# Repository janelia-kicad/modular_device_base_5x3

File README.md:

- [Repository Information](#org3363df3)
  - [Description](#orgd222b12)
- [Images](#orga7265e7)
- [Schematic](#orgfcf2128)
- [Gerbers](#org41eb2be)
- [Bill of Materials](#org5237e5d)
  - [PCB Parts](#org7a5a6dd)
  - [Supplemental Parts](#org5971931)
  - [Vendor Parts Lists](#orgb088364)
- [Supplemental Documentation](#org552370b)
  - [Assembly Instructions](#org9c28d25)

# Repository Information

-   **Name:** modular\_device\_base\_5x3
-   **Version:** 1.2
-   **License:** Open-Source Hardware
-   **URL:** <https://github.com/janelia-kicad/modular_device_base_5x3>
-   **Author:** Peter Polidoro
-   **Email:** peterpolidoro@gmail.com

## Description

This board is the base of 5x3 format modular devices. It is a breakout board for the microprocessor, with connections for power, communication, and top boards.

# Images

# Schematic

[./schematic/modular\_device\_base\_5x3.pdf](./schematic/modular_device_base_5x3.pdf)

# Gerbers

Send gerbers zip file to your favorite PCB manufacturer for fabrication.

[./gerbers/modular\_device\_base\_5x3\_v1.2.zip](./gerbers/modular_device_base_5x3_v1.2.zip)

# Bill of Materials

## PCB Parts

| Item | Reference(s)                         | Quantity | PartNumber          | Vendor  | Description                                           |
|---- |------------------------------------ |-------- |------------------- |------- |----------------------------------------------------- |
| 1    | C1 C2 C3 C4 C5                       | 5        | 445-4536-1-ND       | digikey | CAP CER 10UF 50V 10% X7S 1210                         |
| 2    | C6                                   | 1        | 399-13229-1-ND      | digikey | CAP CER 0.1UF 100V X7R 1210                           |
| 3    | D1 D2                                | 2        | LSM115JE3/TR13CT-ND | digikey | DIODE SCHOTTKY 15V 1A DO214BA                         |
| 4    | D10 D11 D12 D13 D3 D4 D5 D6 D7 D8 D9 | 11       | 568-11697-1-ND      | digikey | DIODE SCHOTTKY 45V 10A CFP15                          |
| 5    | L1                                   | 1        | 350-1712-ND         | digikey | LED 2MM 5V RT ANGLE RED PCMNT                         |
| 6    | L2                                   | 1        | 350-1717-ND         | digikey | LED 2MM 5V RT ANGLE GREEN PCMNT                       |
| 7    | L3                                   | 1        | 350-1719-ND         | digikey | LED 2MM 5V RT ANGLE YELLOW PCMNT                      |
| 8    | MDB1                                 | 2        | S7058-ND            | digikey | 25 Position Header Through Hole Female Socket         |
| 9    | MH1 MH2 MH3 MH4 MH5 MH6 MH7 MH8      | 8        | 36-2027-ND          | digikey | Round Standoff Threaded 4-40 Aluminum 0.500in 0.187in |
| 10   | P1                                   | 1        | CP-063BH-ND         | digikey | CONN PWR JACK DC 2.5X5.5 8A T/H                       |
| 11   | P10 P4 P6 P8                         | 4        | A100903CT-ND        | digikey | CONN HEADER 2POS R/A SMD GOLD                         |
| 12   | P11                                  | 1        | 732-5336-ND         | digikey | CONN HEADER 3 POS RA 2.54                             |
| 13   | P12 P13                              | 2        | SAM10781-ND         | digikey | CONN HEADER 2POS .100in SNGL SMD                      |
| 14   | P2                                   | 1        | ACX1655-ND          | digikey | CONN BNC JACK R/A 75 OHM PCB                          |
| 15   | P3 P5 P7 P9                          | 4        | A100890CT-ND        | digikey | CONN HEADER 3POS R/A SMD GOLD                         |
| 16   | R1                                   | 1        | P6.19KAACT-ND       | digikey | RES SMD 6.19K OHM 1% 1/2W 1210                        |
| 17   | REG1                                 | 1        | 945-1395-5-ND       | digikey | CONV DC/DC 1A 5V OUT SIP VERT                         |
| 18   | SW1 SW2                              | 2        | CKN1860CT-ND        | digikey | SWITCH TACTILE SPST-NO 1VA 32V                        |
| 19   | TEENSY1                              | 1        | 1568-1443-ND        | digikey | TEENSY 3.5                                            |
| 20   | U1                                   | 1        | MAX6817EUT+TCT-ND   | digikey | IC DEBOUNCER SWITCH DUAL SOT23-6                      |

## Supplemental Parts

| Item | Quantity | PartNumber    | Vendor  | Description                                                              |
|---- |-------- |------------- |------- |------------------------------------------------------------------------ |
| 1    | 1        | 62-1187-ND    | digikey | AC/DC DESKTOP ADAPTER 24V 90W                                            |
| 2    | 1        | 993-1037-ND   | digikey | CORD 3COND NEMA PLUG 320-C5                                              |
| 3    | 2        | A106625CT-ND  | digikey | 14 Positions Header Unshrouded Breakaway Connector 0.100in 2 row SMD     |
| 4    | 3        | S1011EC-24-ND | digikey | 14 Positions Header Unshrouded Breakaway Connector 0.100in 1 row Through |
| 5    | 1        | S9001-ND      | digikey | CONN JUMPER SHORTING GOLD FLASH                                          |
| 6    | 1        | AE10342-ND    | digikey | CABLE USB-A TO MICRO USB-B 2M                                            |
| 7    | 2        | 492-1077-ND   | digikey | ROUND SPACER 4 NYLON 7/16in                                              |

## Vendor Parts Lists

[./bom/digikey\_parts.csv](./bom/digikey_parts.csv)

[./bom/supplemental\_digikey\_parts.csv](./bom/supplemental_digikey_parts.csv)

# Supplemental Documentation

## Assembly Instructions

-   Cut the bottom trace on the Teensy board that connects the 5V pads according to these instructions <https://www.pjrc.com/teensy/external_power.html>.
-   Solder through hole header pins into every Teensy 0.1 inch header hole.
-   Solder surface mount header pins onto the bottom of the Teensy making sure they are properly aligned.
-   Solder surface mount and through hole components onto the pcb.
-   Solder the Teensy into the pcb making sure it is properly aligned.
-   Connect header jumper to RED LED enable pins.

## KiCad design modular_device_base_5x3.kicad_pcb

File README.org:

# Created 2018-05-18 Fri 09:39
#+OPTIONS: title:nil author:nil email:nil toc:t |:t ^:nil
* Repository Information

- Name :: modular_device_base_5x3
- Version :: 1.2
- License :: Open-Source Hardware
- URL :: https://github.com/janelia-kicad/modular_device_base_5x3
- Author :: Peter Polidoro
- Email :: peterpolidoro@gmail.com

** Description

This board is the base of 5x3 format modular devices. It is a breakout board
for the microprocessor, with connections for power, communication, and top
boards.

* Images

[[file:./images/top.png]]

[[file:./images/bottom.png]]

* Schematic

[[file:./schematic/modular_device_base_5x3.pdf][./schematic/modular_device_base_5x3.pdf]]

[[file:./schematic/images/schematic00.png]]

* Gerbers

Send gerbers zip file to your favorite PCB manufacturer for fabrication.

[[file:./gerbers/modular_device_base_5x3_v1.2.zip][./gerbers/modular_device_base_5x3_v1.2.zip]]

[[file:./gerbers/images/gerbers00.png]]

[[file:./gerbers/images/gerbers01.png]]

* Bill of Materials

** PCB Parts

| Item | Reference(s)                         | Quantity | PartNumber          | Vendor  | Description                                           |
|------+--------------------------------------+----------+---------------------+---------+-------------------------------------------------------|
|    1 | C1 C2 C3 C4 C5                       |        5 | 445-4536-1-ND       | digikey | CAP CER 10UF 50V 10% X7S 1210                         |
|    2 | C6                                   |        1 | 399-13229-1-ND      | digikey | CAP CER 0.1UF 100V X7R 1210                           |
|    3 | D1 D2                                |        2 | LSM115JE3/TR13CT-ND | digikey | DIODE SCHOTTKY 15V 1A DO214BA                         |
|    4 | D10 D11 D12 D13 D3 D4 D5 D6 D7 D8 D9 |       11 | 568-11697-1-ND      | digikey | DIODE SCHOTTKY 45V 10A CFP15                          |
|    5 | L1                                   |        1 | 350-1712-ND         | digikey | LED 2MM 5V RT ANGLE RED PCMNT                         |
|    6 | L2                                   |        1 | 350-1717-ND         | digikey | LED 2MM 5V RT ANGLE GREEN PCMNT                       |
|    7 | L3                                   |        1 | 350-1719-ND         | digikey | LED 2MM 5V RT ANGLE YELLOW PCMNT                      |
|    8 | MDB1                                 |        2 | S7058-ND            | digikey | 25 Position Header Through Hole Female Socket         |
|    9 | MH1 MH2 MH3 MH4 MH5 MH6 MH7 MH8      |        8 | 36-2027-ND          | digikey | Round Standoff Threaded 4-40 Aluminum 0.500in 0.187in |
|   10 | P1                                   |        1 | CP-063BH-ND         | digikey | CONN PWR JACK DC 2.5X5.5 8A T/H                       |
|   11 | P10 P4 P6 P8                         |        4 | A100903CT-ND        | digikey | CONN HEADER 2POS R/A SMD GOLD                         |
|   12 | P11                                  |        1 | 732-5336-ND         | digikey | CONN HEADER 3 POS RA 2.54                             |
|   13 | P12 P13                              |        2 | SAM10781-ND         | digikey | CONN HEADER 2POS .100in SNGL SMD                      |
|   14 | P2                                   |        1 | ACX1655-ND          | digikey | CONN BNC JACK R/A 75 OHM PCB                          |
|   15 | P3 P5 P7 P9                          |        4 | A100890CT-ND        | digikey | CONN HEADER 3POS R/A SMD GOLD                         |
|   16 | R1                                   |        1 | P6.19KAACT-ND       | digikey | RES SMD 6.19K OHM 1% 1/2W 1210                        |
|   17 | REG1                                 |        1 | 945-1395-5-ND       | digikey | CONV DC/DC 1A 5V OUT SIP VERT                         |
|   18 | SW1 SW2                              |        2 | CKN1860CT-ND        | digikey | SWITCH TACTILE SPST-NO 1VA 32V                        |
|   19 | TEENSY1                              |        1 | 1568-1443-ND        | digikey | TEENSY 3.5                                            |
|   20 | U1                                   |        1 | MAX6817EUT+TCT-ND   | digikey | IC DEBOUNCER SWITCH DUAL SOT23-6                      |

** Supplemental Parts

| Item | Quantity | PartNumber    | Vendor  | Description                                                              |
|------+----------+---------------+---------+--------------------------------------------------------------------------|
|    1 |        1 | 62-1187-ND    | digikey | AC/DC DESKTOP ADAPTER 24V 90W                                            |
|    2 |        1 | 993-1037-ND   | digikey | CORD 3COND NEMA PLUG 320-C5                                              |
|    3 |        2 | A106625CT-ND  | digikey | 14 Positions Header Unshrouded Breakaway Connector 0.100in 2 row SMD     |
|    4 |        3 | S1011EC-24-ND | digikey | 14 Positions Header Unshrouded Breakaway Connector 0.100in 1 row Through |
|    5 |        1 | S9001-ND      | digikey | CONN JUMPER SHORTING GOLD FLASH                                          |
|    6 |        1 | AE10342-ND    | digikey | CABLE USB-A TO MICRO USB-B 2M                                            |
|    7 |        2 | 492-1077-ND   | digikey | ROUND SPACER 4 NYLON 7/16in                                              |

** Vendor Parts Lists

[[file:./bom/digikey_parts.csv][./bom/digikey_parts.csv]]

[[file:./bom/supplemental_digikey_parts.csv][./bom/supplemental_digikey_parts.csv]]

* Supplemental Documentation

** Assembly Instructions

- Cut the bottom trace on the Teensy board that connects the 5V pads according
  to these instructions [[https://www.pjrc.com/teensy/external_power.html]].
- Solder through hole header pins into every Teensy 0.1 inch header hole.
- Solder surface mount header pins onto the bottom of the Teensy making sure
  they are properly aligned.
- Solder surface mount and through hole components onto the pcb.
- Solder the Teensy into the pcb making sure it is properly aligned.
- Connect header jumper to RED LED enable pins.

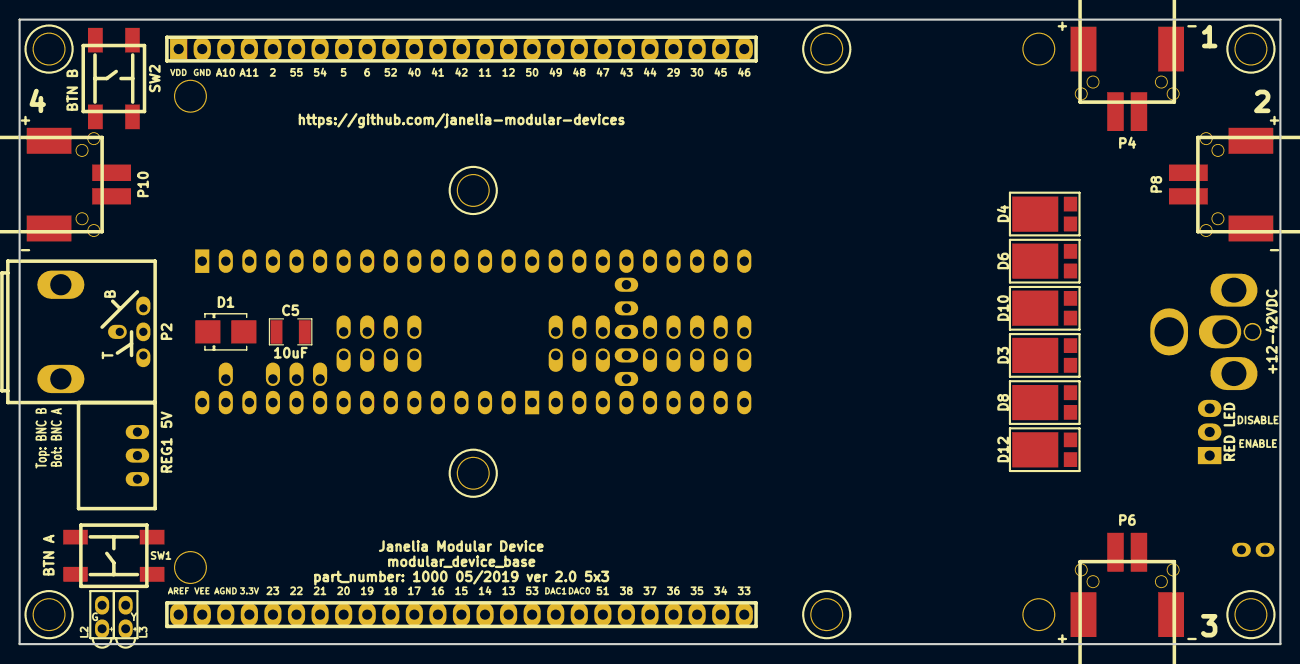
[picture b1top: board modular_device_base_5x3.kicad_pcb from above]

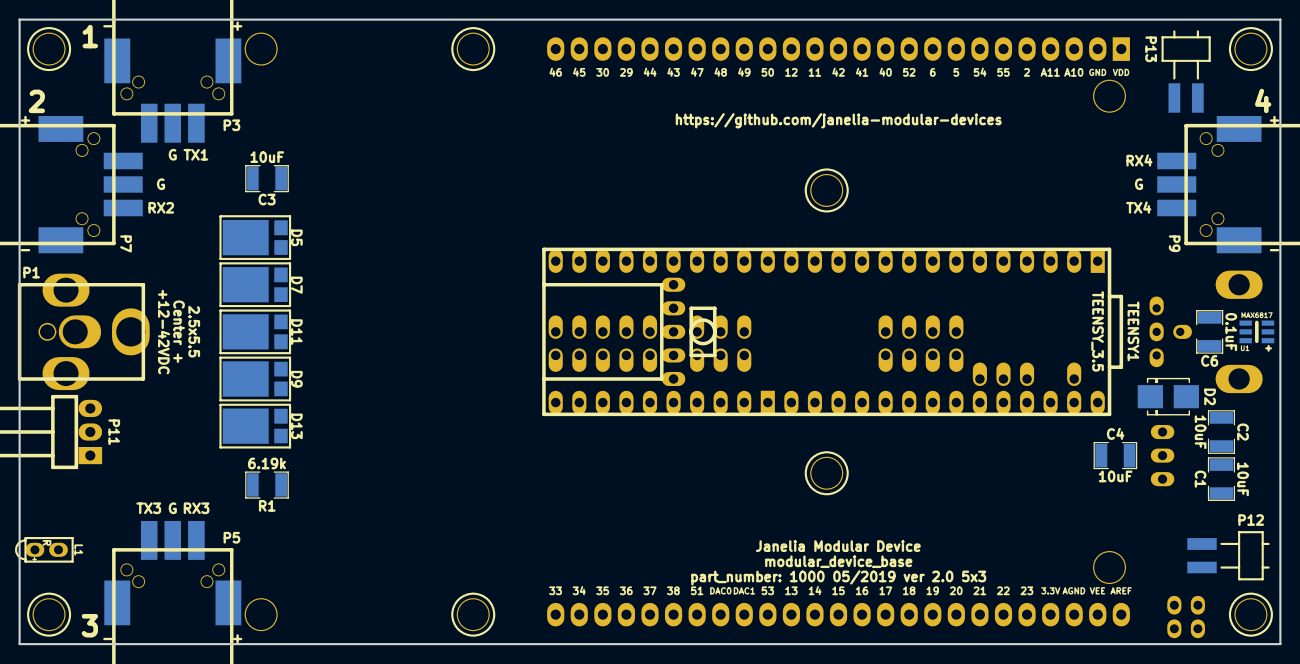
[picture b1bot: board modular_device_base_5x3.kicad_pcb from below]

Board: 2 copper layers, 135.9 x 67.3 mm, 50 parts (23 on the bottom side), 76 nets, no tracks yet.

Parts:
C1, C2, C3, C4, C5: 10uF; SM1210
C6: 0.1uF; SM1210
D1, D2: diode_schottky_15V_1A; DO-214BA
D3, D4, D5, D6, D7, D8, D9, D10, D11, D12, D13: diode_schottky_45V_10A; CFP15
L1: LED_5V_RED_RA; LED_555-2XXX
L2: LED_5V_GRN_RA; LED_555-2XXX
L3: LED_5V_YEL_RA; LED_555-2XXX
MDB1: MODULAR_DEVICE_BASE_5x3_FEMALE; MODULAR_DEVICE_BASE_5X3_FEMALE
MH1, MH2, MH3, MH4, MH5, MH6, MH7, MH8: MNT_HOLE; MOUNTING_HOLE_4-40
P1: PWR_JACK_2.5x5.5; DCJACK_2PIN_HIGHCURRENT
P2: BNC_DOUBLE_RA; BNC_DOUBLE
P3, P5, P7, P9: HEADER_01X03_SMD_RA; Header_3_Pin_SMD_RA
P4, P6, P8, P10: HEADER_01X02_SMD_RA; Header_2_Pin_SMD_RA
P11: HEADER_01X03_RA; Header_3_Pin_RA
P12, P13: HEADER_01X02_SMD_RA_UNSHR; Header_2_Pin_SMD_RA_UNSHR
R1: 6.19k; SM1210
REG1: CONV_DC_DC_5V_1A; DC_DC_CONV_R78C
SW1, SW2: KT_SWITCH
TEENSY1: TEENSY_3.5
U1: MAX6817

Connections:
+5V: C2.1, D2.2, REG1.3
/3V3: C5.1, MDB1.3V3, TEENSY1.3V3
/A10: MDB1.A10, TEENSY1.A10
/A11: MDB1.A11, TEENSY1.A11
/AGND: MDB1.AGND, TEENSY1.AGND
/AREF: MDB1.AREF, TEENSY1.AREF
/BNC_A: P2.1, TEENSY1.57
/BNC_B: P2.3, TEENSY1.56
/BTN_A: P12.1, SW1.2, U1.1
/BTN_A_D: TEENSY1.24, U1.6
/BTN_B: P13.1, SW2.2, U1.3
/BTN_B_D: TEENSY1.25, U1.4
/D2: MDB1.2, TEENSY1.2
/D5: MDB1.5, TEENSY1.5
/D6: MDB1.6, TEENSY1.6
/D11: MDB1.11, TEENSY1.11
/D12: MDB1.12, TEENSY1.12
/D13: MDB1.13, TEENSY1.13
/D14: MDB1.14, TEENSY1.14
/D15: MDB1.15, TEENSY1.15
/D16: MDB1.16, TEENSY1.16
/D17: MDB1.17, TEENSY1.17
/D18: MDB1.18, TEENSY1.18
/D19: MDB1.19, TEENSY1.19
/D20: MDB1.20, TEENSY1.20
/D21: MDB1.21, TEENSY1.21
/D22: MDB1.22, TEENSY1.22
/D23: MDB1.23, TEENSY1.23
/D29: MDB1.29, TEENSY1.29
/D30: MDB1.30, TEENSY1.30
/D33: MDB1.33, TEENSY1.33
/D34: MDB1.34, TEENSY1.34
/D35: MDB1.35, TEENSY1.35
/D36: MDB1.36, TEENSY1.36
/D37: MDB1.37, TEENSY1.37
/D38: MDB1.38, TEENSY1.38
/D40: MDB1.40, TEENSY1.40
/D41: MDB1.41, TEENSY1.41
/D42: MDB1.42, TEENSY1.42
/D43: MDB1.43, TEENSY1.43
/D44: MDB1.44, TEENSY1.44
/D45: MDB1.45, TEENSY1.45
/D46: MDB1.46, TEENSY1.46
/D47: MDB1.47, TEENSY1.47
/D48: MDB1.48, TEENSY1.48
/D49: MDB1.49, TEENSY1.49
/D50: MDB1.50, TEENSY1.50
/D51: MDB1.51, TEENSY1.51
/D52: MDB1.52, TEENSY1.52
/D53: MDB1.53, TEENSY1.53
/D54: MDB1.54, TEENSY1.54
/D55: MDB1.55, TEENSY1.55
/DAC0: MDB1.DAC0, TEENSY1.A21
/DAC1: MDB1.DAC1, TEENSY1.A22
/LED_GRN: L2.1, TEENSY1.26
/LED_YEL: L3.1, TEENSY1.27
/RX1: P3.1, TEENSY1.0
/RX2: P7.1, TEENSY1.9
/RX3: P5.1, TEENSY1.7
/RX4: P9.1, TEENSY1.31
/TX1: P3.3, TEENSY1.1
/TX2: P7.3, TEENSY1.10
/TX3: P5.3, TEENSY1.8
/TX4: P9.3, TEENSY1.32
/V_USB: D1.2, TEENSY1.V_U
GND: C1.2, C2.2, C3.2, C4.2, C5.2, C6.2, L1.2, L2.2, L3.2, MDB1.GND, P1.2, P2.2, P2.4, P3.2, P4.2, P5.2, P6.1, P7.2, P8.2, P9.2, P10.1, P12.2, P13.2, REG1.2, SW1.3, SW2.3, TEENSY1.GND, U1.2
unnamed: L1.1, P11.1
unnamed: P11.2, R1.2
VAA: D3.2, P1.1
VCC: D6.2, D7.1, P4.1
VDD: D4.2, D5.1, MDB1.VDD
VDDA: D10.2, D11.1, P8.1
VEE: C4.1, C6.1, D1.1, D2.1, MDB1.VEE, TEENSY1.V_IN, U1.5
VPP: C1.1, C3.1, D3.1, D4.1, D5.2, D6.1, D7.2, D8.1, D9.2, D10.1, D11.2, D12.1, D13.2, R1.1, REG1.1
VSS: D8.2, D9.1, P6.2
VSSA: D12.2, D13.1, P10.2

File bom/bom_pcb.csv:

Item,Reference(s),Value,Quantity,Description,PartNumber,Vendor
1,C1 C2 C3 C4 C5,10uF,5,CAP CER 10UF 50V 10% X7S 1210,445-4536-1-ND,digikey
2,C6,0.1uF,1,CAP CER 0.1UF 100V X7R 1210,399-13229-1-ND,digikey
3,D1 D2,diode_schottky_15V_1A,2,DIODE SCHOTTKY 15V 1A DO214BA,LSM115JE3/TR13CT-ND,digikey
4,D10 D11 D12 D13 D3 D4 D5 D6 D7 D8 D9,diode_schottky_45V_10A,11,DIODE SCHOTTKY 45V 10A CFP15,568-11697-1-ND,digikey
5,L1,LED_5V_RED_RA,1,LED 2MM 5V RT ANGLE RED PCMNT,350-1712-ND,digikey
6,L2,LED_5V_GRN_RA,1,LED 2MM 5V RT ANGLE GREEN PCMNT,350-1717-ND,digikey
7,L3,LED_5V_YEL_RA,1,LED 2MM 5V RT ANGLE YELLOW PCMNT,350-1719-ND,digikey
8,MDB1,MODULAR_DEVICE_BASE_5x3_FEMALE,2,25 Position Header Through Hole Female Socket,S7058-ND,digikey
9,MH1 MH2 MH3 MH4 MH5 MH6 MH7 MH8,MNT_HOLE,8,Round Standoff Threaded 4-40 Aluminum 0.500in 0.187in,36-2027-ND,digikey
10,P1,PWR_JACK_2.5x5.5,1,CONN PWR JACK DC 2.5X5.5 8A T/H,CP-063BH-ND,digikey
11,P10 P4 P6 P8,HEADER_01X02_SMD_RA,4,CONN HEADER 2POS R/A SMD GOLD,A100903CT-ND,digikey
12,P11,HEADER_01X03_RA,1,CONN HEADER 3 POS RA 2.54,732-5336-ND,digikey
13,P12 P13,HEADER_01X02_SMD_RA_UNSHR,2,CONN HEADER 2POS .100in SNGL SMD,SAM10781-ND,digikey
14,P2,BNC_DOUBLE_RA,1,CONN BNC JACK R/A 75 OHM PCB,ACX1655-ND,digikey
15,P3 P5 P7 P9,HEADER_01X03_SMD_RA,4,CONN HEADER 3POS R/A SMD GOLD,A100890CT-ND,digikey
16,R1,6.19k,1,RES SMD 6.19K OHM 1% 1/2W 1210,P6.19KAACT-ND,digikey
17,REG1,CONV_DC_DC_5V_1A,1,CONV DC/DC 1A 5V OUT SIP VERT,945-1395-5-ND,digikey
18,SW1 SW2,KT_SWITCH,2,SWITCH TACTILE SPST-NO 1VA 32V,CKN1860CT-ND,digikey
19,TEENSY1,TEENSY_3.5,1,TEENSY 3.5,1568-1443-ND,digikey
20,U1,MAX6817,1,IC DEBOUNCER SWITCH DUAL SOT23-6,MAX6817EUT+TCT-ND,digikey

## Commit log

2017-02-03 Initial commit.
2017-02-03 footprints: -> modular_device_base_5x3:.
2017-02-03 Added TEENSY_3.5 footprint.
2017-02-06 Added Teensy3.5 component.
2017-02-06 Progress towards v1.0.
2017-02-07 Progress towards new modifications.
2017-02-08 Finished design ver 1.0.
2017-02-08 Updated boms.
2017-03-24 Updated documentation.
2017-05-23 Added components and footprints.
2017-05-23 Progress towards v1.1.
2017-05-24 More progress towards v1.1.
2017-05-25 Completed v1.1.
2017-05-26 Added standoffs to bom.
2017-05-26 Moved edges of MDB_5x3 footprint.
2017-08-08 Progress towards v1.2.
2017-08-09 Finished v1.2.
2017-09-13 Updated 0.1uF capacitors.
2017-09-22 Removed extra libraries.
2017-10-04 Updated LibDir.
2018-01-08 Updated to v4.
2018-01-08 Added v4 files.
2018-01-08 Removed *cache* and *rescue*.
2018-01-08 Updated gitignore.
2018-03-09 Update license from software to hardware.
2018-04-12 README.md -> README.org.
2018-04-19 Added .DS_Store to .gitignore.
2018-04-19 Added images.
2018-04-19 Chnaged image size and aspect ratio.
2018-04-19 top -> front. bottom -> back.
2018-04-20 front -> top. back -> bottom.
2018-05-16 Added documentation.
2018-05-16 Remove frame ref from gerber images.
2018-05-17 Updated submodules.
2018-05-17 Added assembly instructions.
2018-05-17 Renamed to gerbers.pdf.
2018-05-18 Updated README.
2018-08-12 Marked extra Teensy 3.5 Pins.
2018-08-12 Updated teensy pin markings.
2018-08-12 Removed v4 files.
2018-08-23 Added digikey_order.
2018-08-23 Added supplemental parts.
2018-08-24 Removed F.SilkS from pads.
2018-08-27 Removed *.SilkS from pads.
2018-11-02 Added README.md.
2019-05-24 Add schematics
2019-06-03 teensy_3.5_plus -> teensy_3.5
2019-06-03 Add exported components
2019-06-03 Import exported components
2019-06-03 Update processor component
2021-09-16 Update email address
2021-09-21 Remove ignored files
2022-02-22 Add guix files
2022-02-23 Add guix documentation
